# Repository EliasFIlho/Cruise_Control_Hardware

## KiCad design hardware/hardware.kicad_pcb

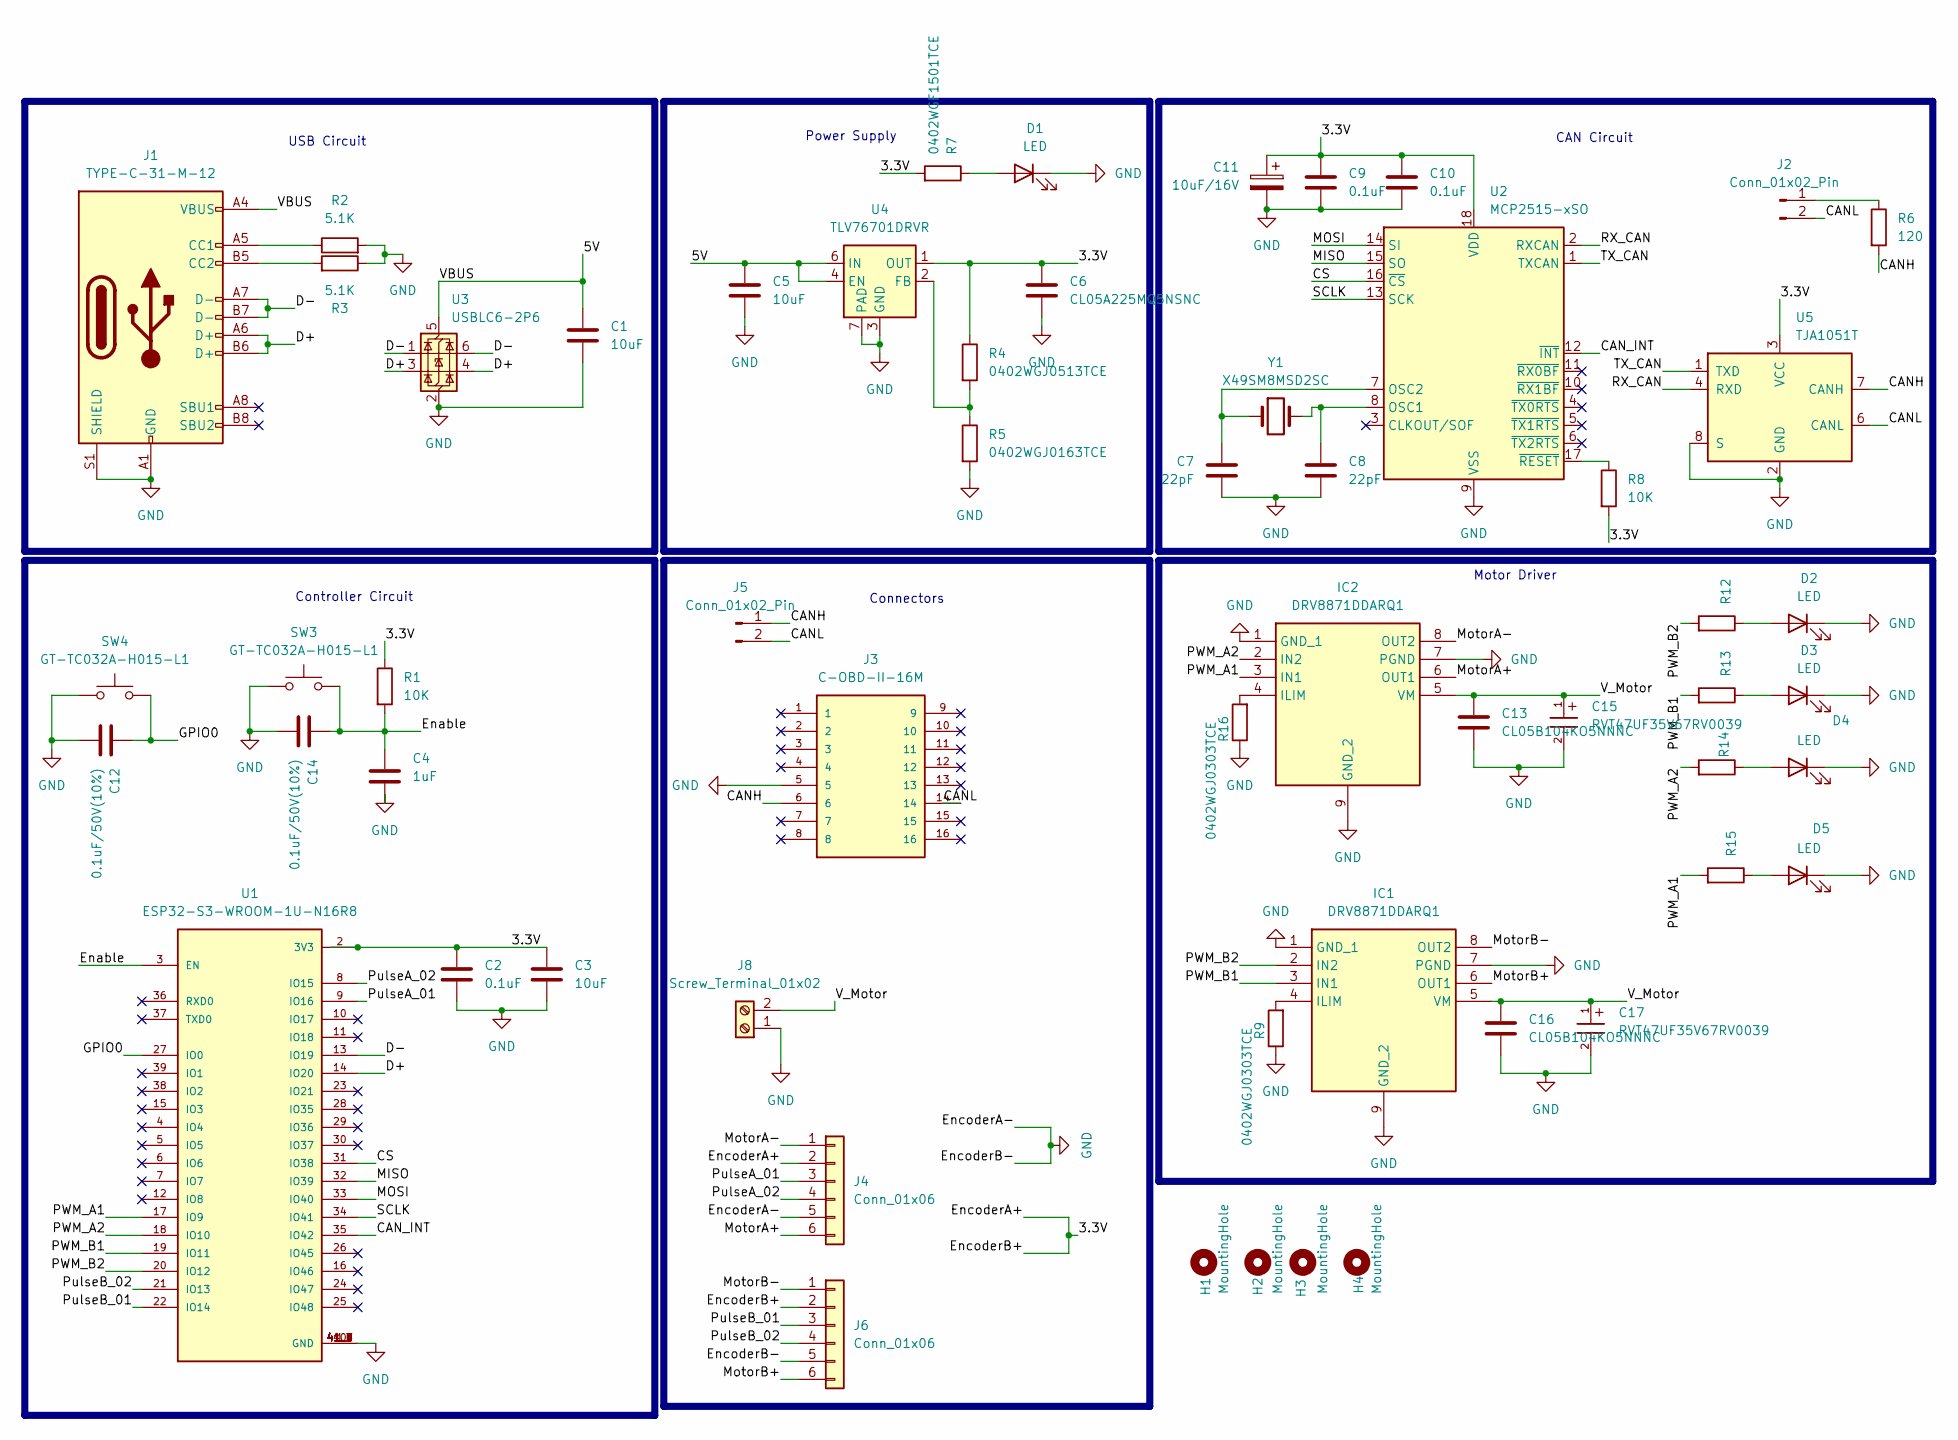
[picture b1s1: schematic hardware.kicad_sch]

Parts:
C1, C5: 10uF; C_0402_1005Metric
C2, C9, C10: 0.1uF; C_0805_2012Metric_Pad1.18x1.45mm_HandSolder
C3: 10uF; C_0805_2012Metric_Pad1.18x1.45mm_HandSolder
C4: 1uF; C_0805_2012Metric_Pad1.18x1.45mm_HandSolder
C6: CL05A225MQ5NSNC; C_0402_1005Metric
C7, C8: 22pF; C_0805_2012Metric_Pad1.18x1.45mm_HandSolder
C11: 10uF/16V; C_0805_2012Metric_Pad1.18x1.45mm_HandSolder
C12, C14: 0.1uF/50V(10%); C_0805_2012Metric_Pad1.18x1.45mm_HandSolder
C13, C16: CL05B104KO5NNNC; C_0402_1005Metric
C15, C17: RVT47UF35V67RV0039; CP_Elec_6.3x5.4
D1, D2, D3, D4, D5: LED; LED_0805_2012Metric_Pad1.15x1.40mm_HandSolder
H1, H2, H3, H4: MountingHole; MountingHole_2.2mm_M2
IC1, IC2: DRV8871DDARQ1; SOIC127P600X170-9N; Mouser Part Number 595-DRV8871DDARQ1
J1: TYPE-C-31-M-12; USB_C_Receptacle_G-Switch_GT-USB-7010ASV
J2, J5: Conn_01x02_Pin; PinHeader_1x02_P1.00mm_Vertical
J3: C-OBD-II-16M; COMTECH_C-OBD-II-16M; PARTREV A
J4, J6: Conn_01x06; JST_EH_S6B-EH_1x06_P2.50mm_Horizontal
J8: Screw_Terminal_01x02; PhoenixContact_MSTBA_2,5_2-G-5,08_1x02_P5.08mm_Horizontal
R1, R8: 10K; R_0805_2012Metric_Pad1.20x1.40mm_HandSolder
R2, R3: 5.1K; R_0805_2012Metric_Pad1.20x1.40mm_HandSolder
R4: 0402WGJ0513TCE; R_0402_1005Metric
R5: 0402WGJ0163TCE; R_0402_1005Metric
R6: 120; R_0805_2012Metric_Pad1.20x1.40mm_HandSolder
R7, R12, R13, R14, R15: 0402WGF1501TCE; R_0402_1005Metric
R9, R16: 0402WGJ0303TCE; R_0402_1005Metric
SW3, SW4: GT-TC032A-H015-L1; SW_SPST_B3U-1000P
U1: ESP32-S3-WROOM-1U-N16R8; XCVR_ESP32-S3-WROOM-1U-N16R8; PARTREV v1.1
U2: MCP2515-xSO; SOIC-18W_7.5x11.6mm_P1.27mm
U3: USBLC6-2P6; SOT-666
U4: TLV76701DRVR; WSON-6-1EP_2x2mm_P0.65mm_EP1x1.6mm_ThermalVias
U5: TJA1051T; SOIC-8_3.9x4.9mm_P1.27mm
Y1: X49SM8MSD2SC; Crystal_SMD_HC49-SD

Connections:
/3.3V: C2.1, C3.1, C6.1, C9.1, C10.1, C11.1, J4.2, J6.2, R1.1, R4.1, R7.2, R8.2, U1.2 (3V3), U2.18 (VDD), U4.1 (OUT), U5.3 (VCC)
/5V: C1.1, C5.1, J1.A4 (VBUS), J1.A9 (VBUS), J1.B4 (VBUS), J1.B9 (VBUS), U3.5 (VBUS), U4.4 (EN), U4.6 (IN)
/CANH: J3.6, J5.1, R6.2, U5.7 (CANH)
/CANL: J2.2, J3.14, J5.2, U5.6 (CANL)
/CAN_INT: U1.35 (IO42), U2.12 (~INT)
/CS: U1.31 (IO38), U2.16 (~CS)
/D+: J1.A6 (D+), J1.B6 (D+), U1.14 (IO20), U3.3 (I/O2), U3.4 (I/O2)
/D-: J1.A7 (D-), J1.B7 (D-), U1.13 (IO19), U3.1 (I/O1), U3.6 (I/O1)
/Enable: C4.1, C14.1, R1.2, SW3.2, U1.3 (EN)
/GPIO0: C12.1, SW4.2, U1.27 (IO0)
/MISO: U1.32 (IO39), U2.15 (SO)
/MOSI: U1.33 (IO40), U2.14 (SI)
/MotorA+: IC2.6 (OUT1), J4.6
/MotorA-: IC2.8 (OUT2), J4.1
/MotorB+: IC1.6 (OUT1), J6.6
/MotorB-: IC1.8 (OUT2), J6.1
/PWM_A1: IC2.3 (IN1), R15.2, U1.17 (IO9)
/PWM_A2: IC2.2 (IN2), R14.2, U1.18 (IO10)
/PWM_B1: IC1.3 (IN1), R13.2, U1.19 (IO11)
/PWM_B2: IC1.2 (IN2), R12.2, U1.20 (IO12)
/PulseA_01: J4.3, U1.9 (IO16)
/PulseA_02: J4.4, U1.8 (IO15)
/PulseB_01: J6.3, U1.22 (IO14)
/PulseB_02: J6.4, U1.21 (IO13)
/RX_CAN: U2.2 (RXCAN), U5.4 (RXD)
/SCLK: U1.34 (IO41), U2.13 (SCK)
/TX_CAN: U2.1 (TXCAN), U5.1 (TXD)
/V_Motor: C13.1, C15.1, C16.1, C17.1, IC1.5 (VM), IC2.5 (VM), J8.2
GND: C1.2, C2.2, C3.2, C4.2, C5.2, C6.2, C7.1, C8.2, C9.2, C10.2, C11.2, C12.2, C13.2, C14.2, C15.2, C16.2, C17.2, D1.1 (K), D2.1 (K), D3.1 (K), D4.1 (K), D5.1 (K), IC1.1 (GND_1), IC1.7 (PGND), IC1.9 (GND_2), IC2.1 (GND_1), IC2.7 (PGND), IC2.9 (GND_2), J1.A1 (GND), J1.A12 (GND), J1.B1 (GND), J1.B12 (GND), J1.S1 (SHIELD), J3.5, J4.5, J6.5, J8.1, R2.2, R3.1, R5.2, R9.1, R16.1, SW3.1, SW4.1, U1.1 (GND), U1.40 (GND), U1.41_1 (GND), U1.41_2 (GND), U1.41_3 (GND), U1.41_4 (GND), U1.41_5 (GND), U1.41_6 (GND), U1.41_7 (GND), U1.41_8 (GND), U1.41_9 (GND), U2.9 (VSS), U3.2 (GND), U4.3 (GND), U4.5 (GND), U4.7 (PAD), U5.2 (GND), U5.8 (S)
unnamed: D1.2 (A), R7.1
unnamed: D2.2 (A), R12.1
unnamed: D3.2 (A), R13.1
unnamed: D4.2 (A), R14.1
unnamed: D5.2 (A), R15.1
unnamed: IC1.4 (ILIM), R9.2
unnamed: IC2.4 (ILIM), R16.2
unnamed: J1.A5 (CC1), R2.1
unnamed: J1.B5 (CC2), R3.2
unnamed: J2.1, R6.1
unnamed: C8.1, U2.8 (OSC1), Y1.2
unnamed: C7.2, U2.7 (OSC2), Y1.1
unnamed: R8.1, U2.17 (~RESET)
unnamed: R4.2, R5.1, U4.2 (FB)

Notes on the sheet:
USB Circuit
Power Supply
Motor Driver
CAN Circuit
Controller Circuit
Connectors

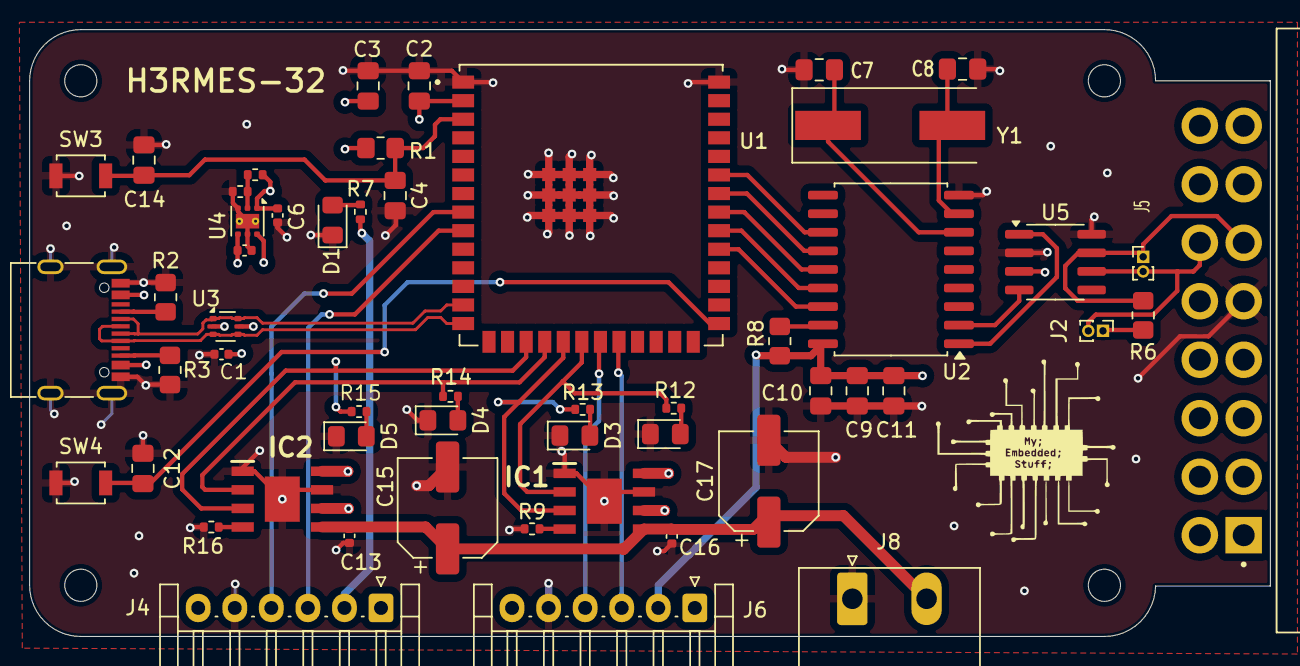
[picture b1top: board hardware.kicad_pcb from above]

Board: 4 copper layers, 84.8 x 41.5 mm, 57 parts (0 on the bottom side), 43 nets.

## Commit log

2025-05-10 Motor driver and connector
2025-05-10 Added Leds and moved from 2 to 4 layers pcb
2025-05-14 Changed motor driver IC from DRV8411 to DRV8871 PCB updated as well added manufacture values in schematics
2025-05-15 version 1
